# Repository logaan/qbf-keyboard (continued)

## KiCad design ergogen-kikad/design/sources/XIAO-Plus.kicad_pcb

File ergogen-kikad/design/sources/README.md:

# Controller source snapshot

`XIAO-Plus.kicad_pcb` and `XIAO-Plus.kicad_sch` are unmodified Seeed reference-project snapshots linked by the [official XIAO BLE documentation](https://wiki.seeedstudio.com/XIAO_BLE/). Their SHA-256 hashes are recorded in `../assembly.json`. The shared project contains optional Sense components; its footprint locations are dimensional references, not a guarantee of non-Sense population or exact supplied-module heights.

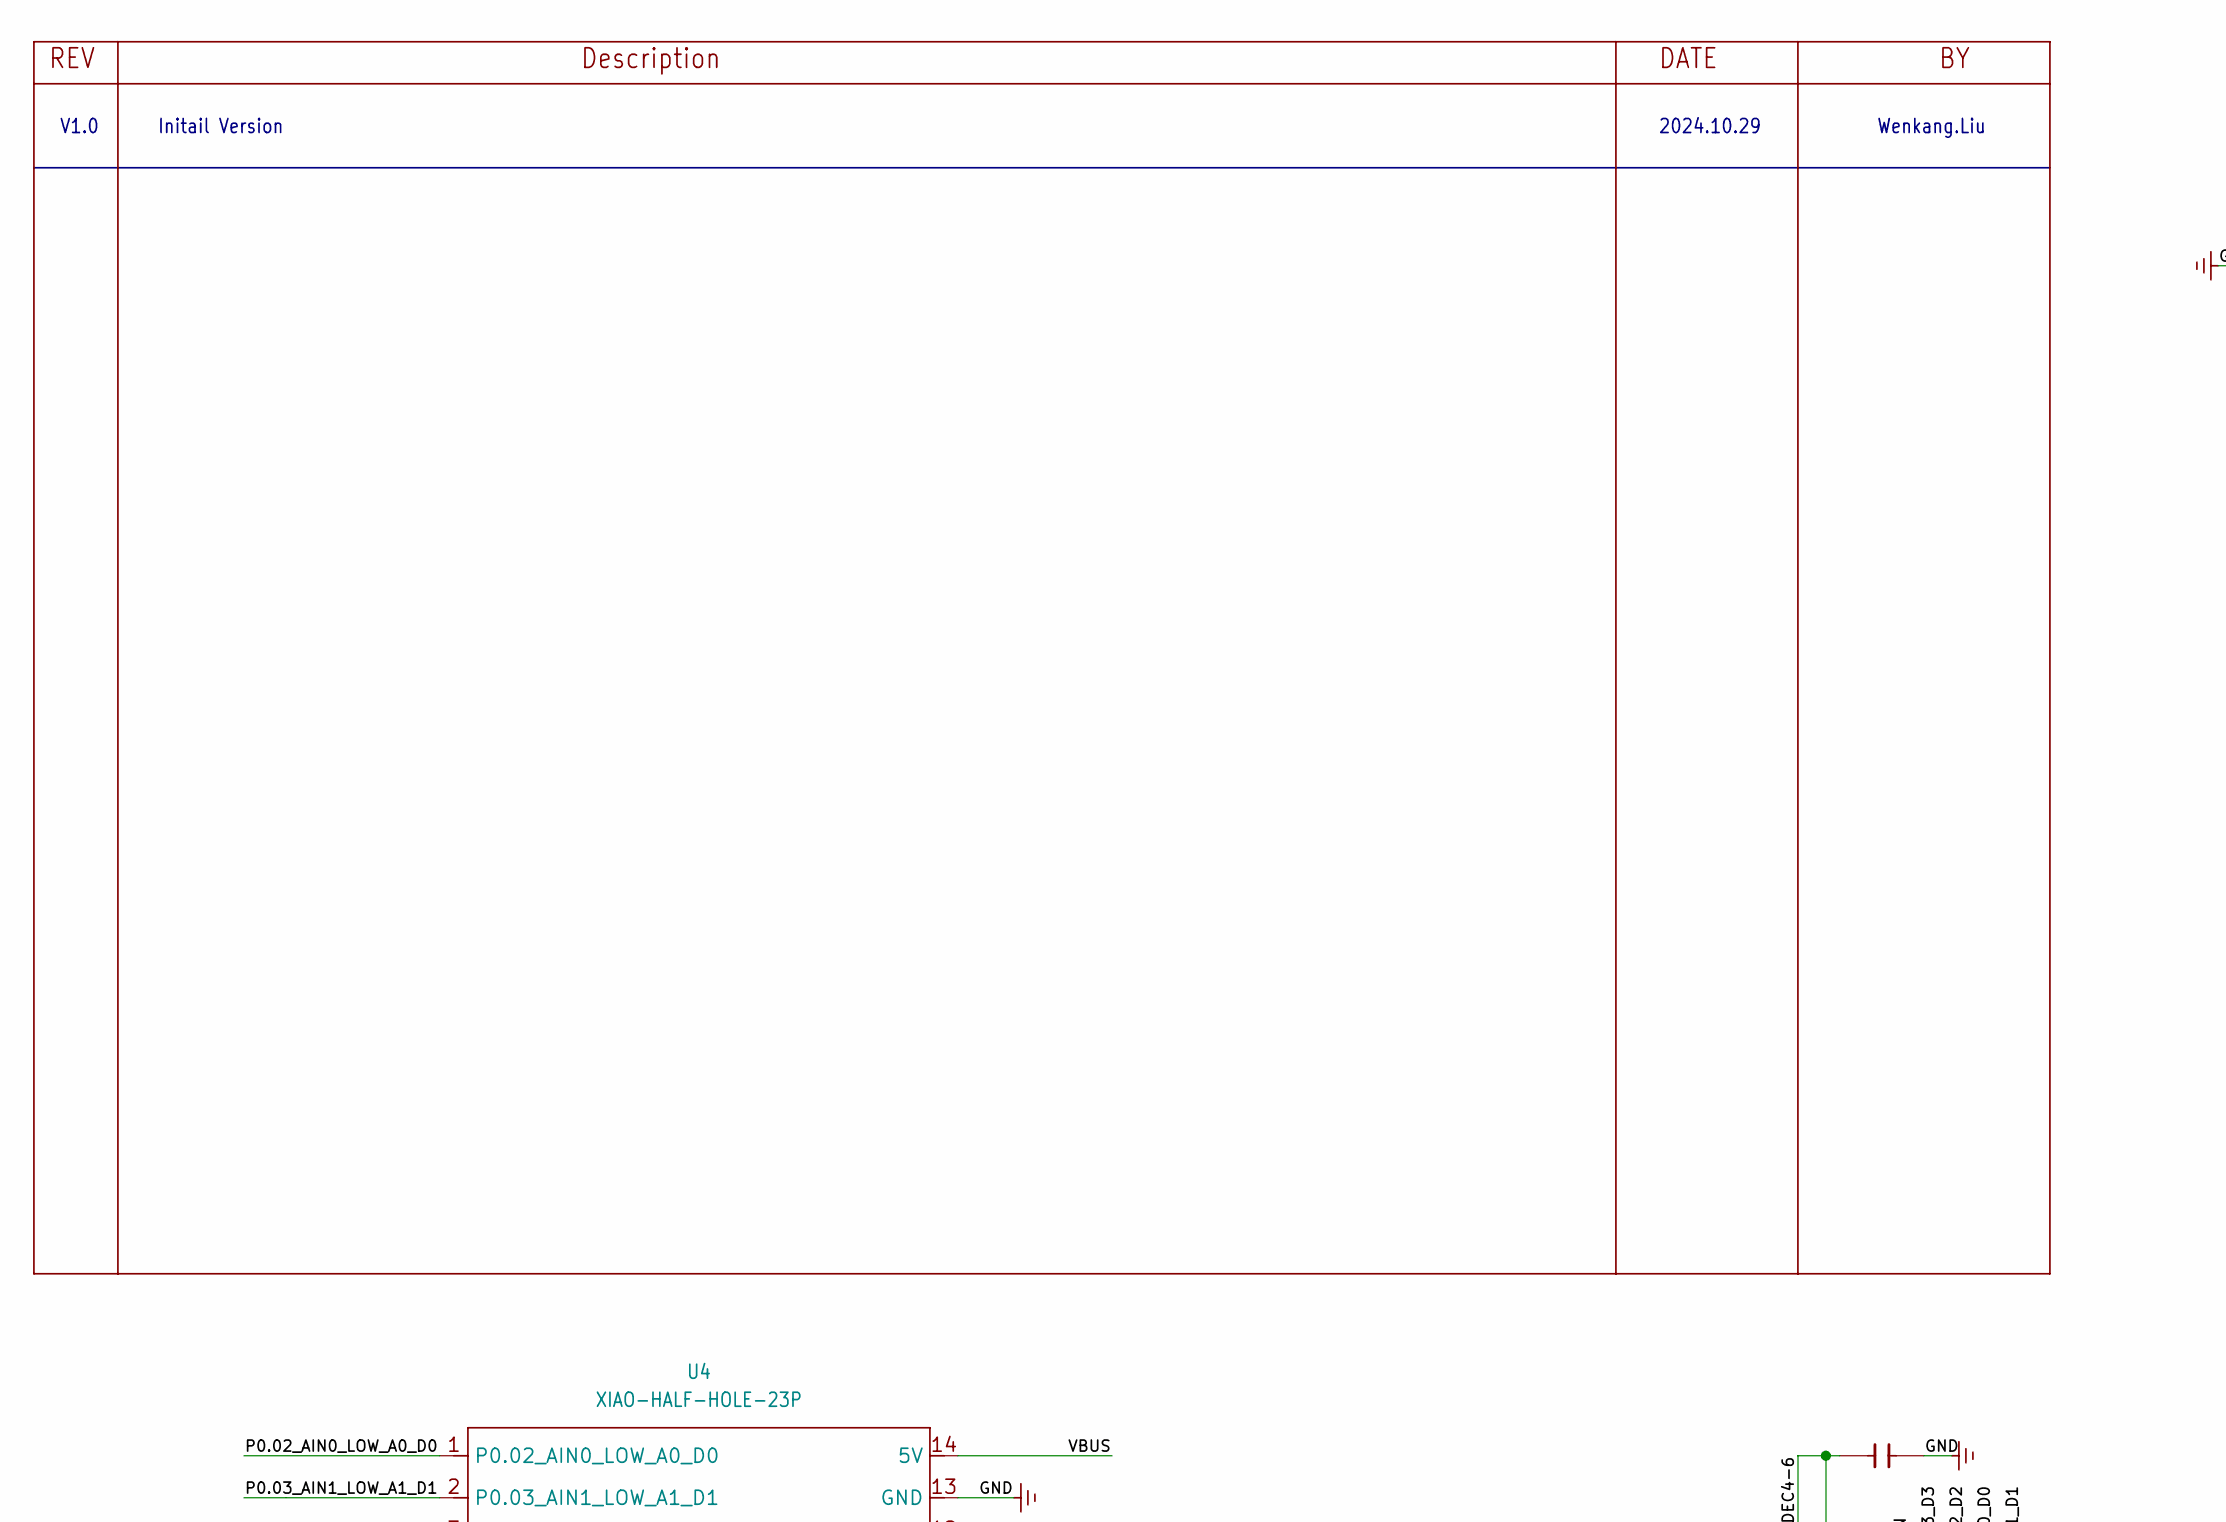
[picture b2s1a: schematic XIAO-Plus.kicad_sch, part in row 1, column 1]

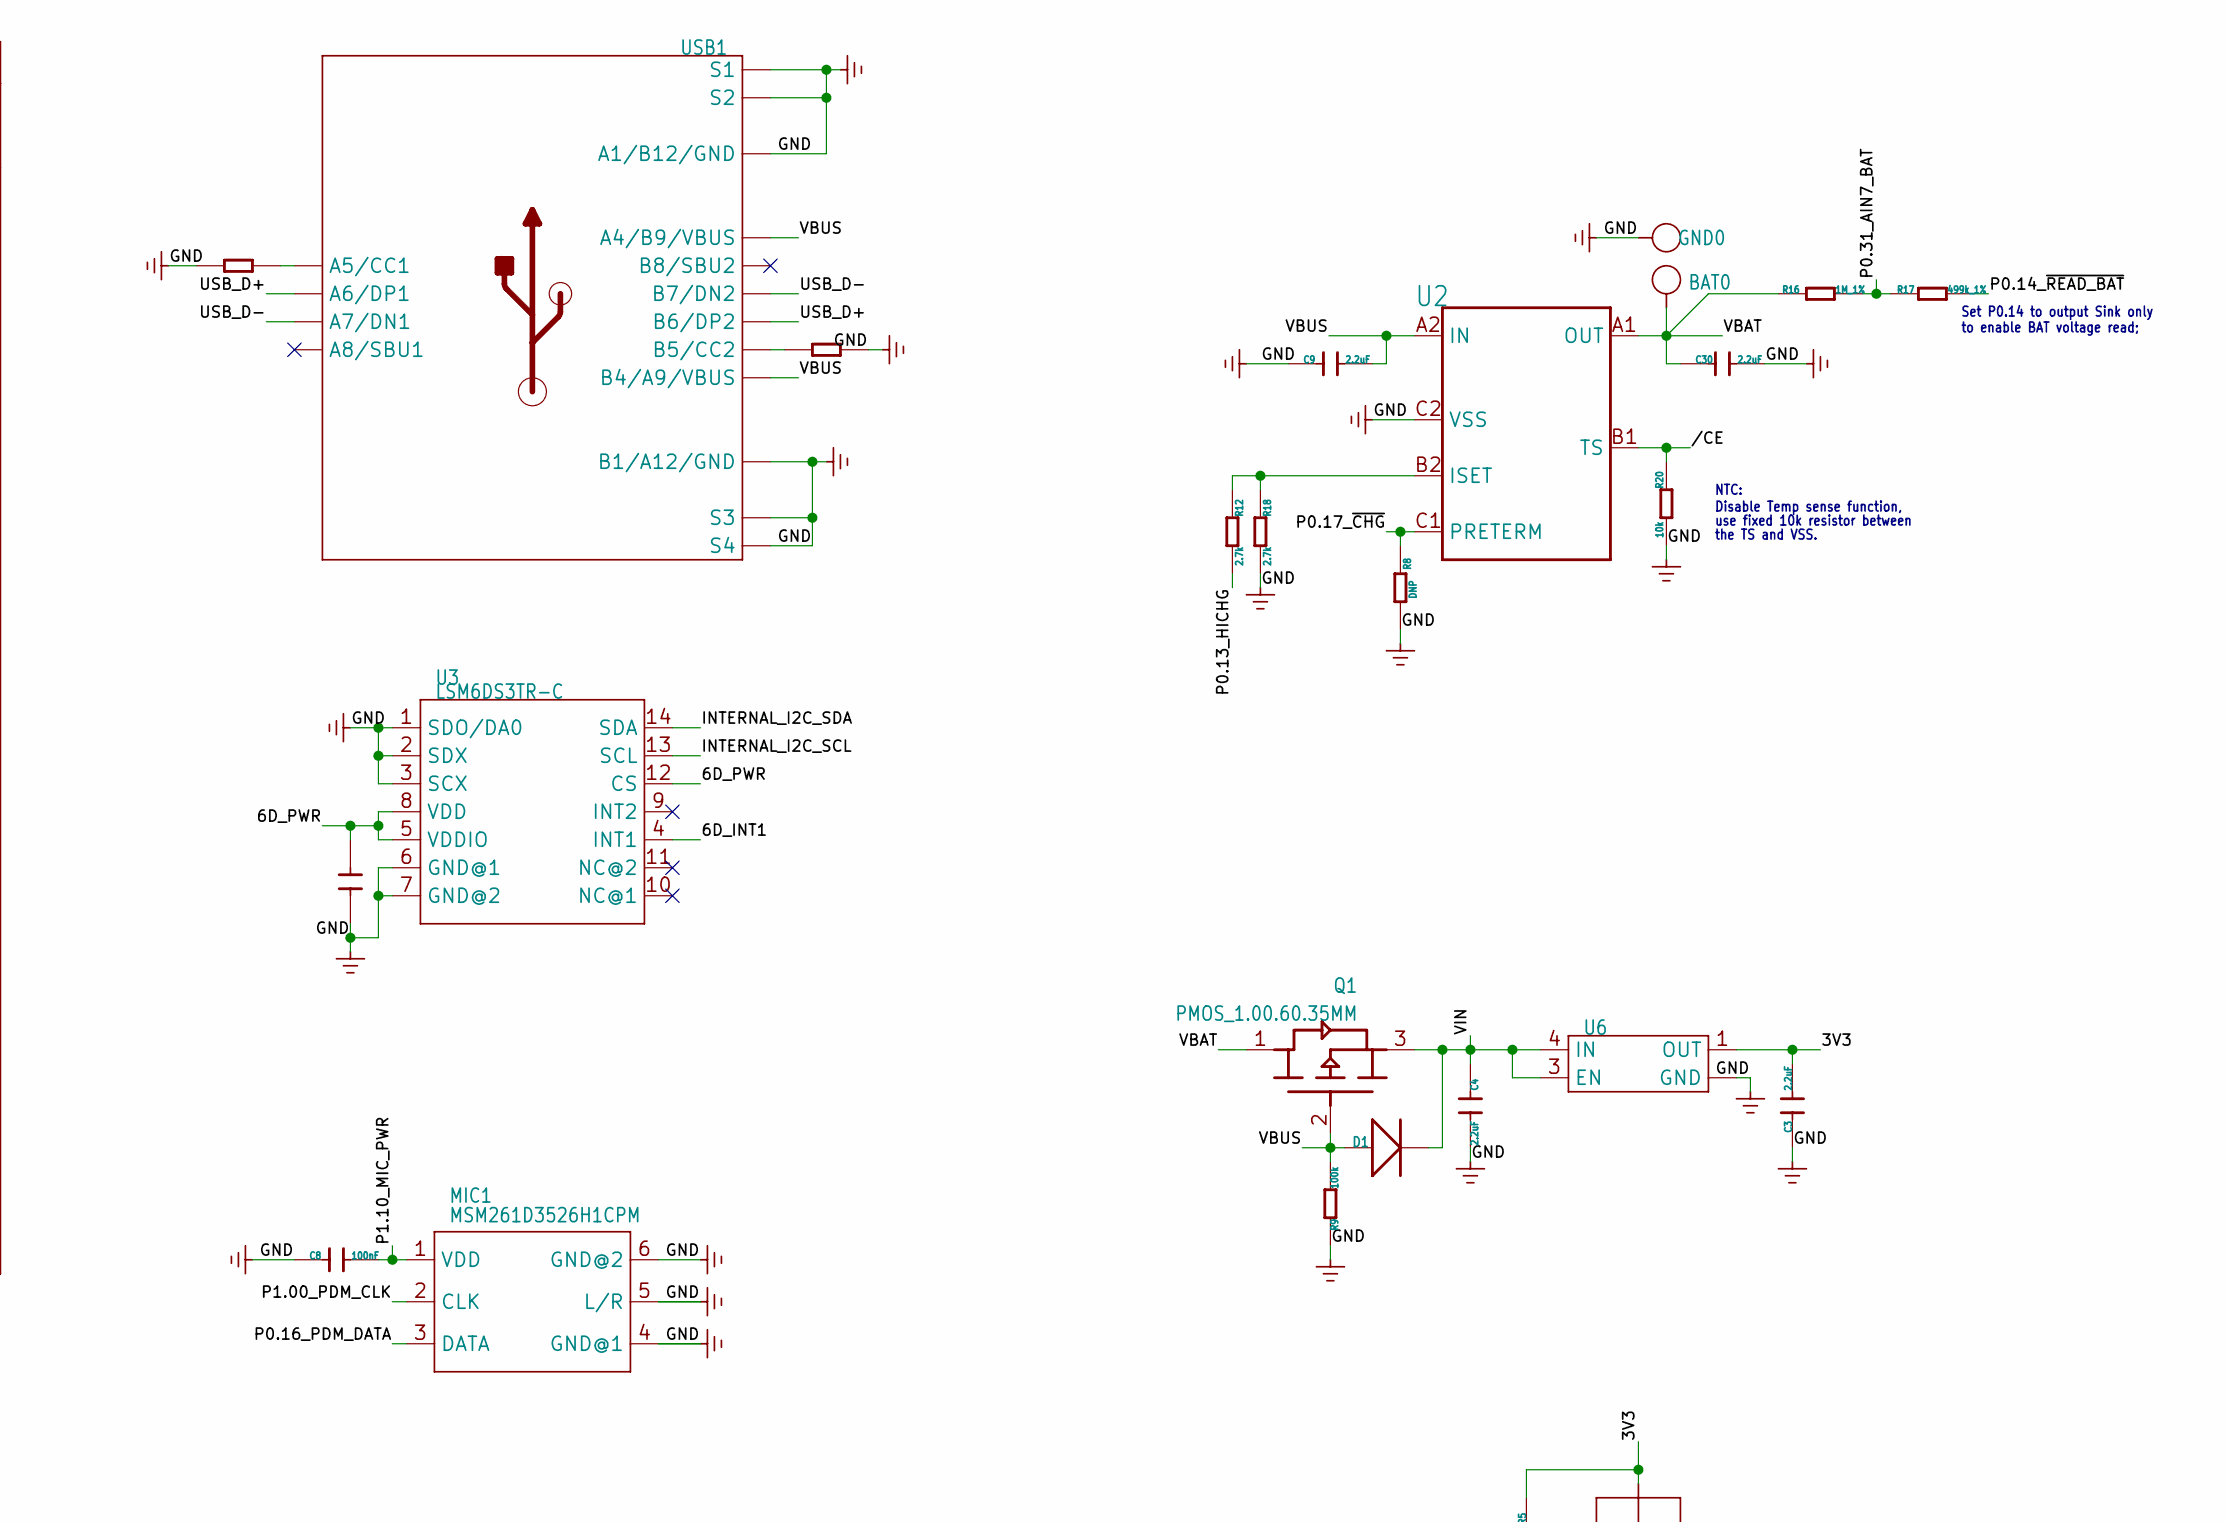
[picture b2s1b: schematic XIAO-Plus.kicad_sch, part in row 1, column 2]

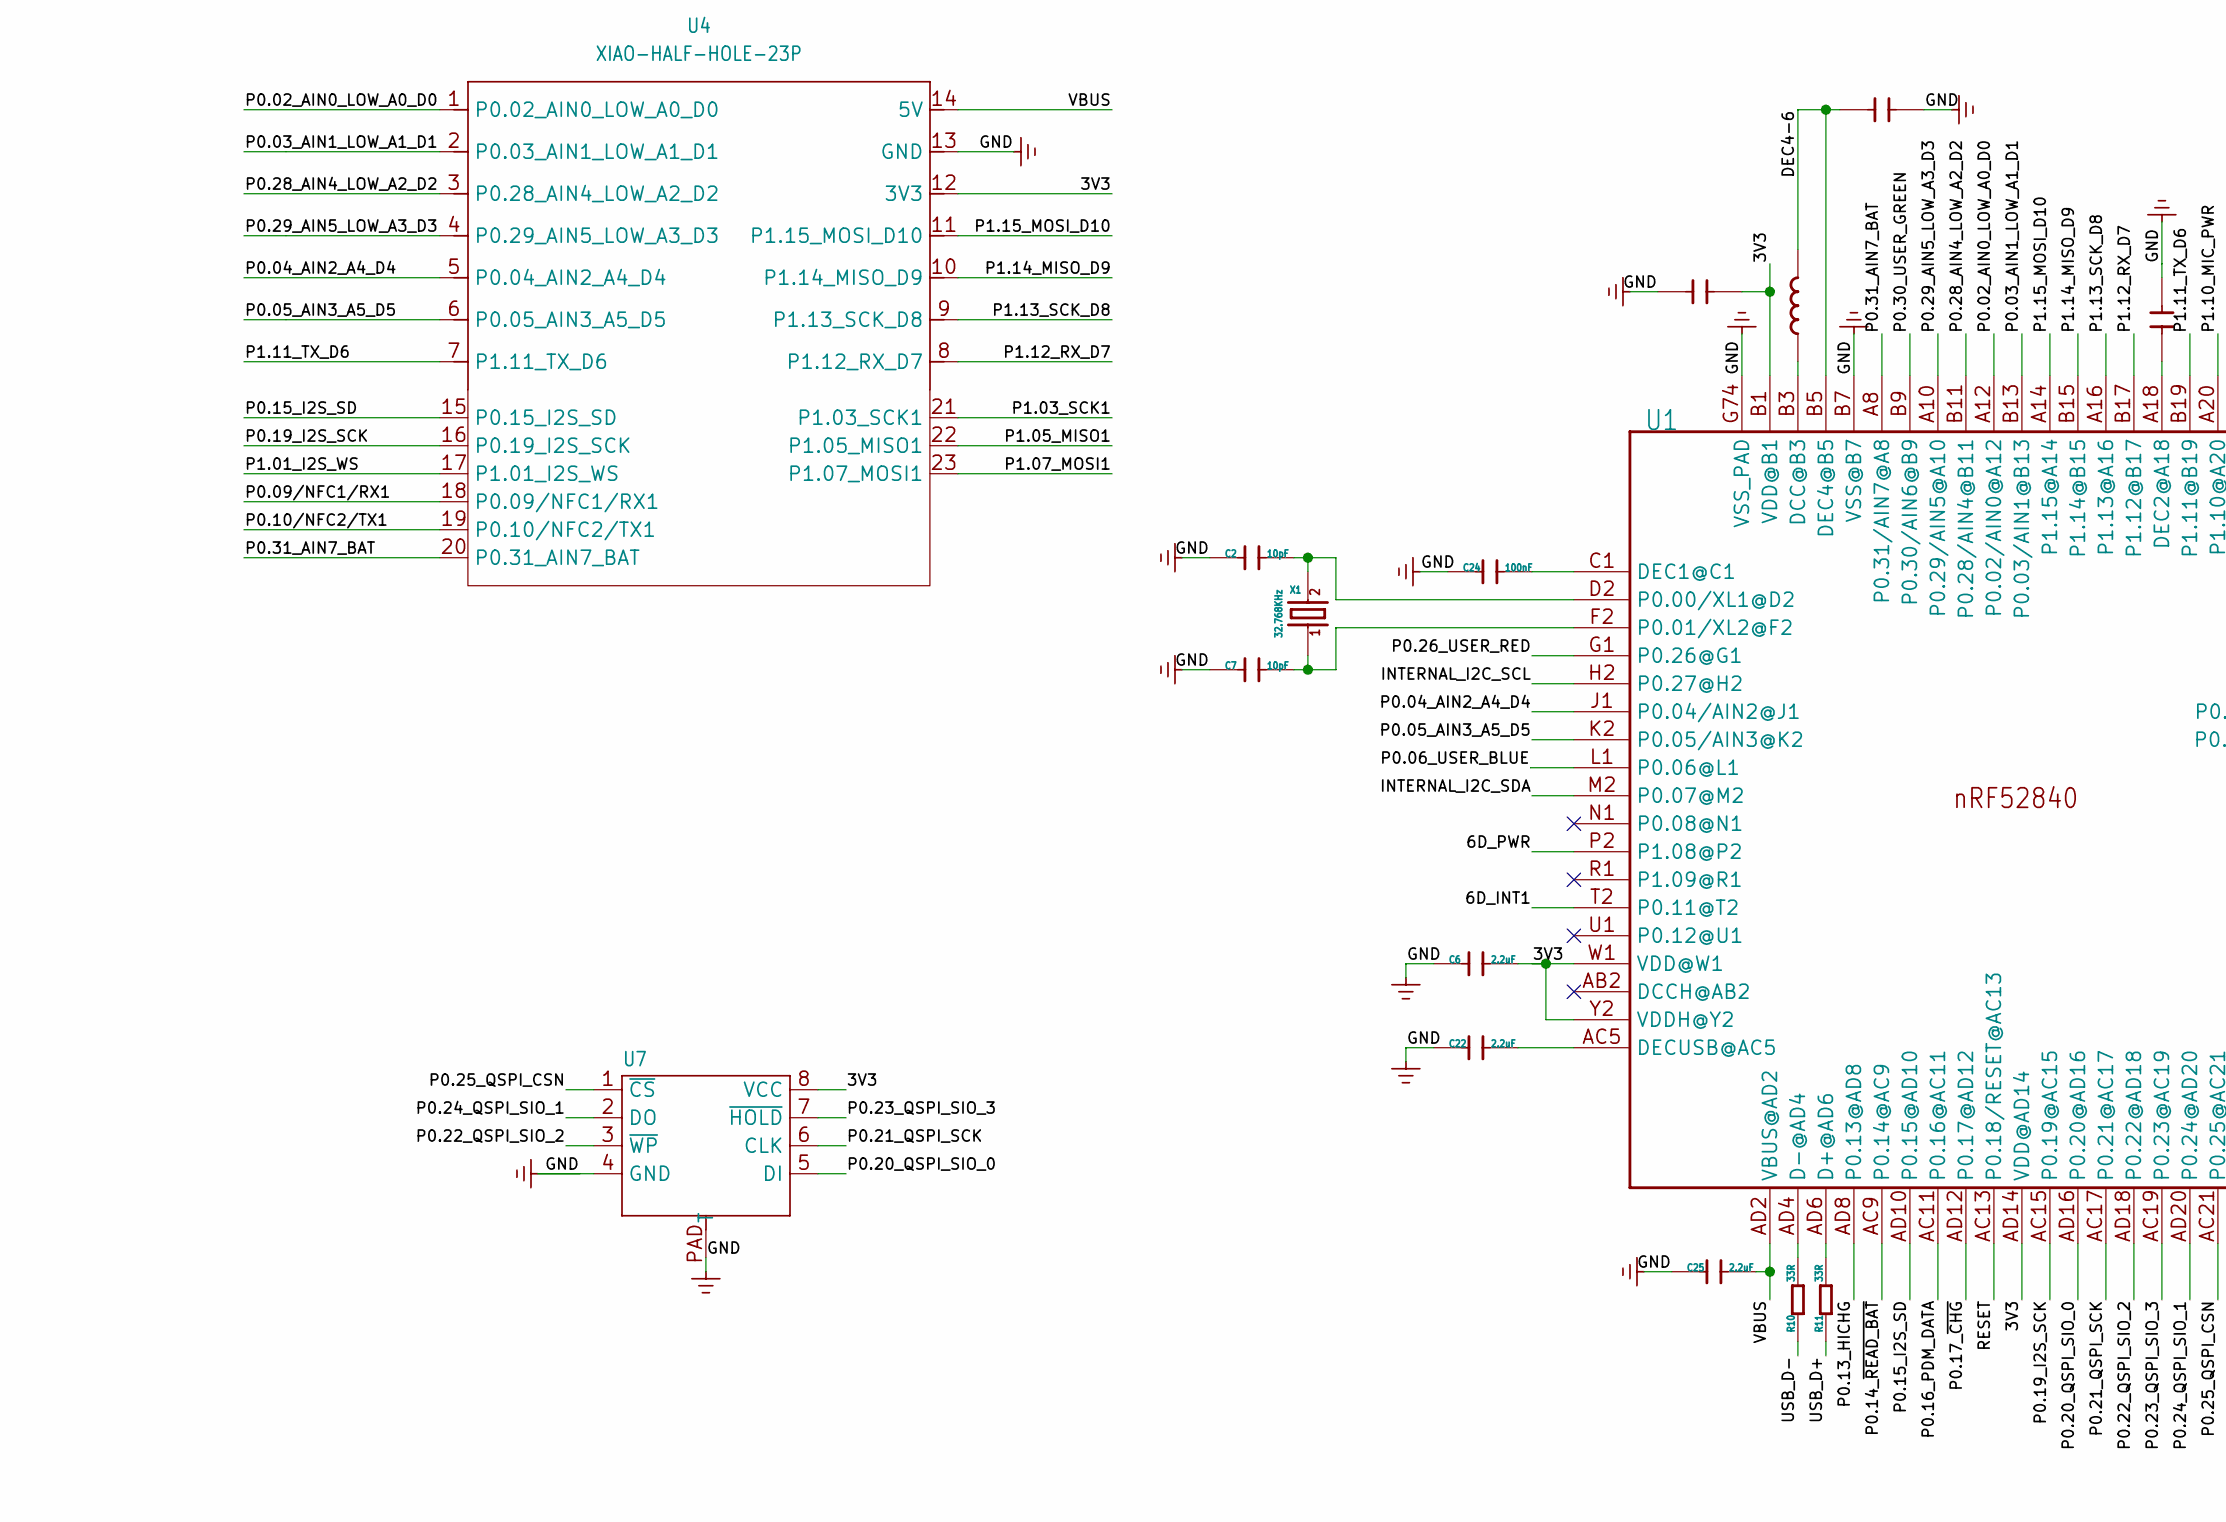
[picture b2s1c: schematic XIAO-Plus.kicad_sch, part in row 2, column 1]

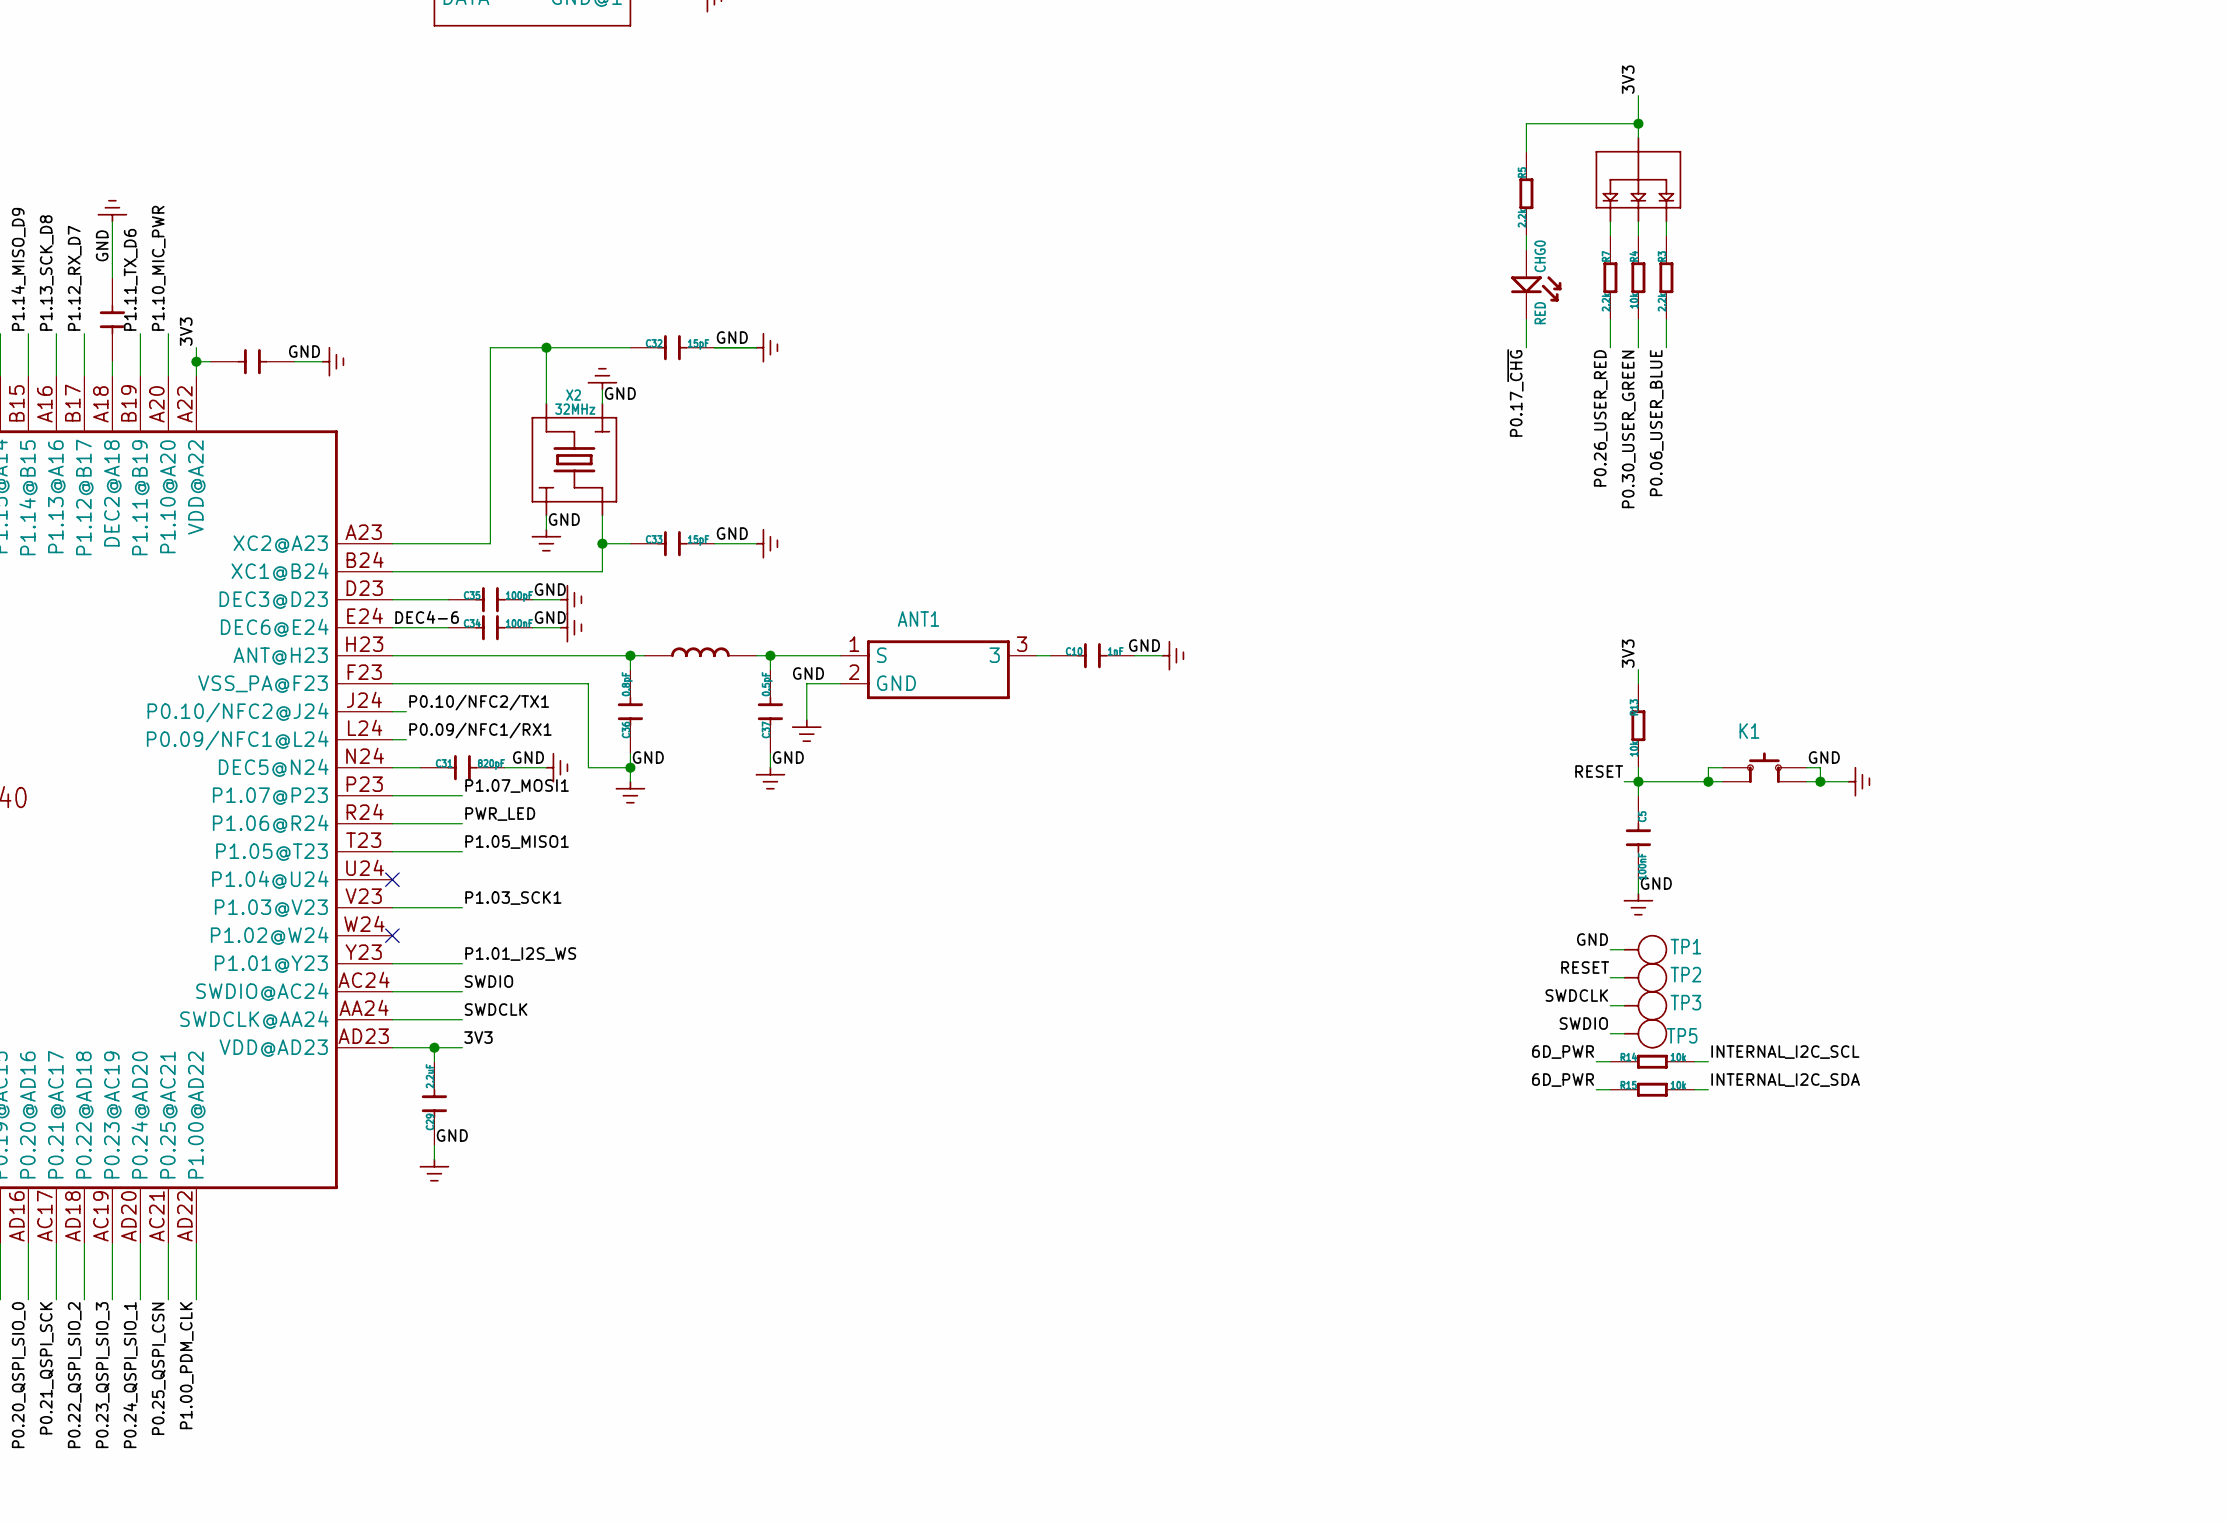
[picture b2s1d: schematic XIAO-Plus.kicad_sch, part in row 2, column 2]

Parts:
ANT1: ANTENNA-AN3216; ANT-SMD3P-3.2X1.6X1.04MM
BAT0: TEST-POINT'4080'; TP-80X40MIL
C1, C5, C8, C24, C34: 100nF; C0201
C2, C7: 10pF; C0201
C3, C4, C6, C9, C22, C25, C29, C30, C39, C41, C42: 2.2uF; C0201
C10: 1nF; C0402
C31: 820pF; C0201
C32, C33: 15pF; C0201
C35: 100pF; C0201
C36: 0.8pF; C0201
C37: 0.5pF; C0201
C38: 4.7nH; L0201
C40: DNP; C0201
CHG0: RED; LED-0402
D1: DIODE'0603'; SOD-523
GND0: GND; TP-80X40MIL
K1: BUTTON-4P; SW4-SMD-2.8-2.6X1.6X0.53MM
L3: 10uH; L0603
MIC1: MSM261D3526H1CPM; MIC6P-3.5X2.65X0.94MM
Q1: PMOS_1.00.60.35MM; PMOS_1.0*0.6*0.35MM
R1, R2: 5.1k; R0201
R3, R5, R7: 2.2k; R0201
R4, R13, R14, R15, R20: 10k; R0201
R8: DNP; R0201
R9: 100k; R0201
R10, R11: 33R; R0201
R12, R18: 2.7k; R0201
R16: 1M_1%; R0201
R17: 499k_1%; R0201
RGB6: RGB; 4P1010
TP1, TP2, TP3, TP5: TEST-POINT'4545'; TP-D45MIL
U1: NRF52840_QF; AQFN50P700X700X85_HS-74N
U2: BQ25100; BQ25101_DSBGA_6_BQ25101
U3: LSM6DS3TR-C; LGA14-0.5-2.5X3X0.86MM
U4: XIAO-HALF-HOLE-23P; MOUDLE23P-XIAO-HALF-HOLE
U6: 3.3V; X2SON-4
U7: DNP; USON2X3_8
USB1: USB2.0-TYPE-C
X1: 32.768KHz; X2-SMD-L1.6X1.0X0.5MM
X2: 32MHz; 4P1612

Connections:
/3V3: C3.2, C6.2, C29.2, C39.1, C41.2, R5.1, R13.1, RGB6.+, U1.A22 (VDD@A22), U1.AD14 (VDD@AD14), U1.AD23 (VDD@AD23), U1.B1 (VDD@B1), U1.W1 (VDD@W1), U1.Y2 (VDDH@Y2), U4.12 (3V3), U6.1 (OUT), U7.8 (VCC)
/6D_INT1: U1.T2 (P0.11@T2), U3.4 (INT1)
/6D_PWR: C1.2, R14.1, R15.1, U1.P2 (P1.08@P2), U3.5 (VDDIO), U3.8 (VDD), U3.12 (CS)
/DEC4-6: C34.1, C42.1, L3.2, U1.B5 (DEC4@B5), U1.E24 (DEC6@E24)
/INTERNAL_I2C_SCL: R14.2, U1.H2 (P0.27@H2), U3.13 (SCL)
/INTERNAL_I2C_SDA: R15.2, U1.M2 (P0.07@M2), U3.14 (SDA)
/P0.02_AIN0_LOW_A0_D0: U1.A12 (P0.02/AIN0@A12), U4.1 (PA02_A0_D0)
/P0.03_AIN1_LOW_A1_D1: U1.B13 (P0.03/AIN1@B13), U4.2 (PA4_A1_D1)
/P0.04_AIN2_A4_D4: U1.J1 (P0.04/AIN2@J1), U4.5 (PA8_A4_D4_SDA)
/P0.05_AIN3_A5_D5: U1.K2 (P0.05/AIN3@K2), U4.6 (PA9_A5_D5_SCL)
/P0.06_USER_BLUE: R3.2, U1.L1 (P0.06@L1)
/P0.09/NFC1/RX1: U1.L24 (P0.09/NFC1@L24), U4.18
/P0.10/NFC2/TX1: U1.J24 (P0.10/NFC2@J24), U4.19
/P0.13_HICHG: R12.2, U1.AD8 (P0.13@AD8)
/P0.14_~READ_BAT: R17.2, U1.AC9 (P0.14@AC9)
/P0.15_I2S_SD: U1.AD10 (P0.15@AD10), U4.15
/P0.16_PDM_DATA: MIC1.3 (DATA), U1.AC11 (P0.16@AC11)
/P0.17_~CHG: CHG0.-, R8.1, U1.AD12 (P0.17@AD12), U2.C1 (PRETERM)
/P0.19_I2S_SCK: U1.AC15 (P0.19@AC15), U4.16
/P0.20_QSPI_SIO_0: U1.AD16 (P0.20@AD16), U7.5 (DI)
/P0.21_QSPI_SCK: U1.AC17 (P0.21@AC17), U7.6 (CLK)
/P0.22_QSPI_SIO_2: U1.AD18 (P0.22@AD18), U7.3 (~WP)
/P0.23_QSPI_SIO_3: U1.AC19 (P0.23@AC19), U7.7 (~HOLD)
/P0.24_QSPI_SIO_1: U1.AD20 (P0.24@AD20), U7.2 (DO)
/P0.25_QSPI_CSN: U1.AC21 (P0.25@AC21), U7.1 (~CS)
/P0.26_USER_RED: R7.2, U1.G1 (P0.26@G1)
/P0.28_AIN4_LOW_A2_D2: U1.B11 (P0.28/AIN4@B11), U4.3 (PA10_A2_D2)
/P0.29_AIN5_LOW_A3_D3: U1.A10 (P0.29/AIN5@A10), U4.4 (PA11_A3_D3)
/P0.30_USER_GREEN: R4.2, U1.B9 (P0.30/AIN6@B9)
/P0.31_AIN7_BAT: R16.2, R17.1, U1.A8 (P0.31/AIN7@A8), U4.20
/P1.00_PDM_CLK: MIC1.2 (CLK), U1.AD22 (P1.00@AD22)
/P1.01_I2S_WS: U1.Y23 (P1.01@Y23), U4.17
/P1.03_SCK1: U1.V23 (P1.03@V23), U4.21
/P1.05_MISO1: U1.T23 (P1.05@T23), U4.22
/P1.07_MOSI1: U1.P23 (P1.07@P23), U4.23
/P1.10_MIC_PWR: C8.2, MIC1.1 (VDD), U1.A20 (P1.10@A20)
/P1.11_TX_D6: U1.B19 (P1.11@B19), U4.7 (PB08_A6_D6_TX)
/P1.12_RX_D7: U1.B17 (P1.12@B17), U4.8 (PB09_A7_D7_RX)
/P1.13_SCK_D8: U1.A16 (P1.13@A16), U4.9 (PA7_A8_D8_SCK)
/P1.14_MISO_D9: U1.B15 (P1.14@B15), U4.10 (PA5_A9_D9_MISO)
/P1.15_MOSI_D10: U1.A14 (P1.15@A14), U4.11 (PA6_A10_D10_MOSI)
/PWR_LED: U1.R24 (P1.06@R24)
/RESET: C5.1, K1.1 (A0), K1.3 (A1), R13.2, TP2.T, U1.AC13 (P0.18/RESET@AC13)
/SWDCLK: TP3.T, U1.AA24 (SWDCLK@AA24)
/SWDIO: TP5.T, U1.AC24 (SWDIO@AC24)
/USB_D+: R11.1, USB1.A6 (A6/DP1), USB1.B6 (B6/DP2)
/USB_D-: R10.1, USB1.A7 (A7/DN1), USB1.B7 (B7/DN2)
/VBAT: BAT0.1 (T), C30.1, Q1.1 (D), R16.1, U2.A1 (OUT)
/VBUS: C9.2, C25.2, D1.+, Q1.2 (G), R9.2, U1.AD2 (VBUS@AD2), U2.A2 (IN), U4.14 (5V), USB1.A4_B9 (A4/B9/VBUS), USB1.B4_A9 (B4/A9/VBUS)
/VIN: C4.1, D1.-, Q1.3 (S), U6.3 (EN), U6.4 (IN)
//CE: R20.1, U2.B1 (TS)
GND_POWER: ANT1.2 (GND), C1.1, C2.1, C3.1, C4.2, C5.2, C6.1, C7.1, C8.1, C9.1, C10.2, C22.1, C24.1, C25.1, C29.1, C30.2, C31.2, C32.2, C33.2, C34.2, C35.2, C36.1, C37.1, C39.2, C40.2, C41.1, C42.2, GND0.1 (T), K1.2 (B0), K1.4 (B1), MIC1.4 (GND@1), MIC1.5 (L/R), MIC1.6 (GND@2), R1.2, R2.1, R8.2, R9.1, R18.2, R20.2, TP1.T, U1.B7 (VSS@B7), U1.F23 (VSS_PA@F23), U1.G74 (VSS_PAD), U2.C2 (VSS), U3.1 (SDO/DA0), U3.2 (SDX), U3.3 (SCX), U3.6 (GND@1), U3.7 (GND@2), U4.13 (GND), U6.2 (GND), U6.T (GND), U7.4 (GND), U7.PAD (T), USB1.A1_B12 (A1/B12/GND), USB1.B1_A12 (B1/A12/GND), USB1.S1, USB1.S2, USB1.S3, USB1.S4, USB1.S5 (S1), USB1.S6 (S2), X2.2 (1), X2.4 (3)
unnamed: ANT1.3, C10.1
unnamed: ANT1.1 (S), C37.2, C38.2
unnamed: CHG0.+, R5.2
unnamed: R3.1, RGB6.B-
unnamed: R4.1, RGB6.G-
unnamed: R7.1, RGB6.R-
unnamed: C36.2, C38.1, U1.H23 (ANT@H23)
unnamed: R11.2, U1.AD6 (D+@AD6)
unnamed: R10.2, U1.AD4 (D-@AD4)
unnamed: L3.1, U1.B3 (DCC@B3)
unnamed: C24.2, U1.C1 (DEC1@C1)
unnamed: C40.1, U1.A18 (DEC2@A18)
unnamed: C35.1, U1.D23 (DEC3@D23)
unnamed: C31.1, U1.N24 (DEC5@N24)
unnamed: C22.2, U1.AC5 (DECUSB@AC5)
unnamed: C2.2, U1.D2 (P0.00/XL1@D2), X1.2
unnamed: C7.2, U1.F2 (P0.01/XL2@F2), X1.1
unnamed: C33.1, U1.B24 (XC1@B24), X2.1 (2)
unnamed: C32.1, U1.A23 (XC2@A23), X2.3 (4)
unnamed: R12.1, R18.1, U2.B2 (ISET)
unnamed: R1.1, USB1.A5 (A5/CC1)
unnamed: R2.2, USB1.B5 (B5/CC2)

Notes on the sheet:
the TS and VSS.
Disable Temp sense function,
NTC:
use fixed 10k resistor between
Initail Version
Wenkang.Liu
V1.0
2024.10.29
Set P0.14 to output Sink only to enable BAT voltage read;

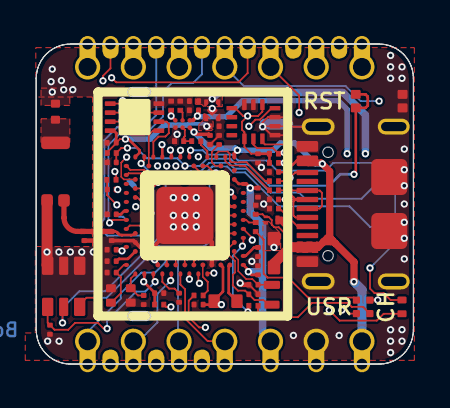
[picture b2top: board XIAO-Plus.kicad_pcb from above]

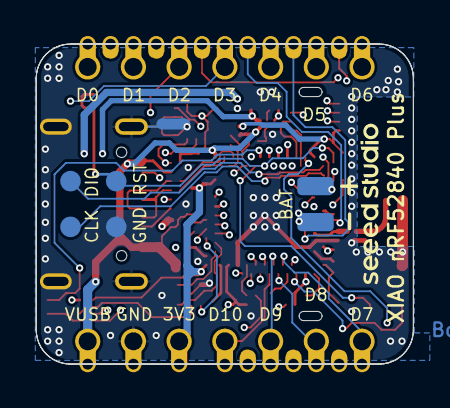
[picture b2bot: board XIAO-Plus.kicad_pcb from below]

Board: 4 copper layers, 21.0 x 17.8 mm, 68 parts (6 on the bottom side), 73 nets.

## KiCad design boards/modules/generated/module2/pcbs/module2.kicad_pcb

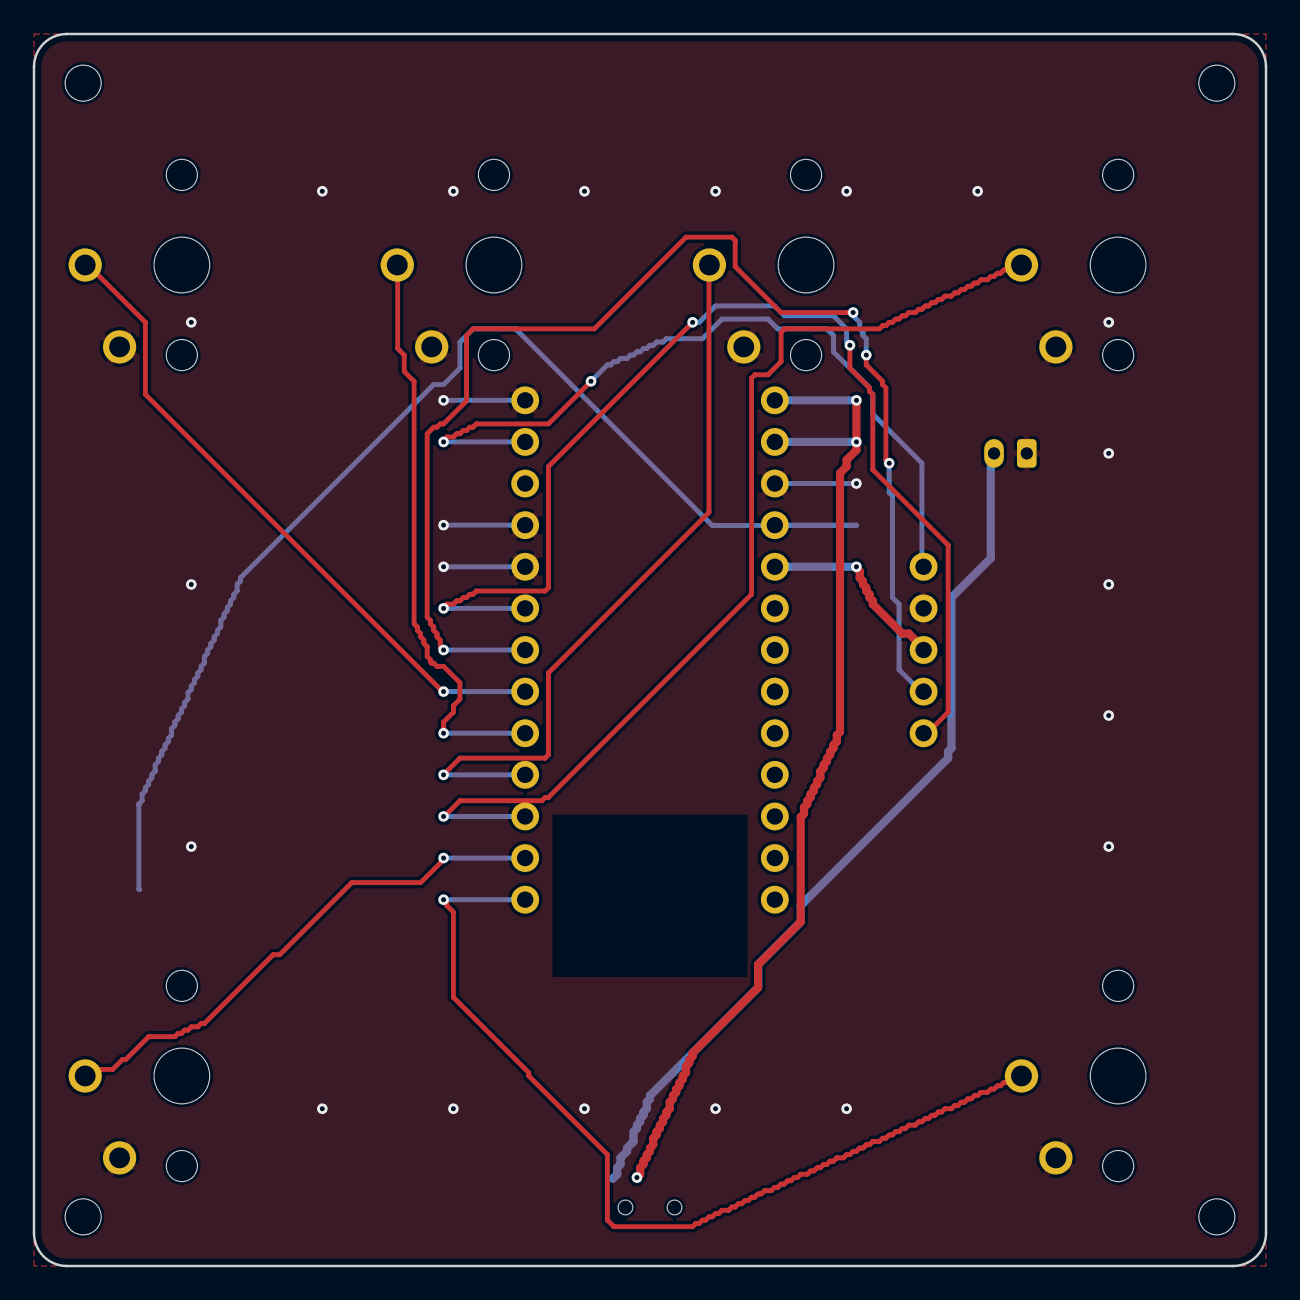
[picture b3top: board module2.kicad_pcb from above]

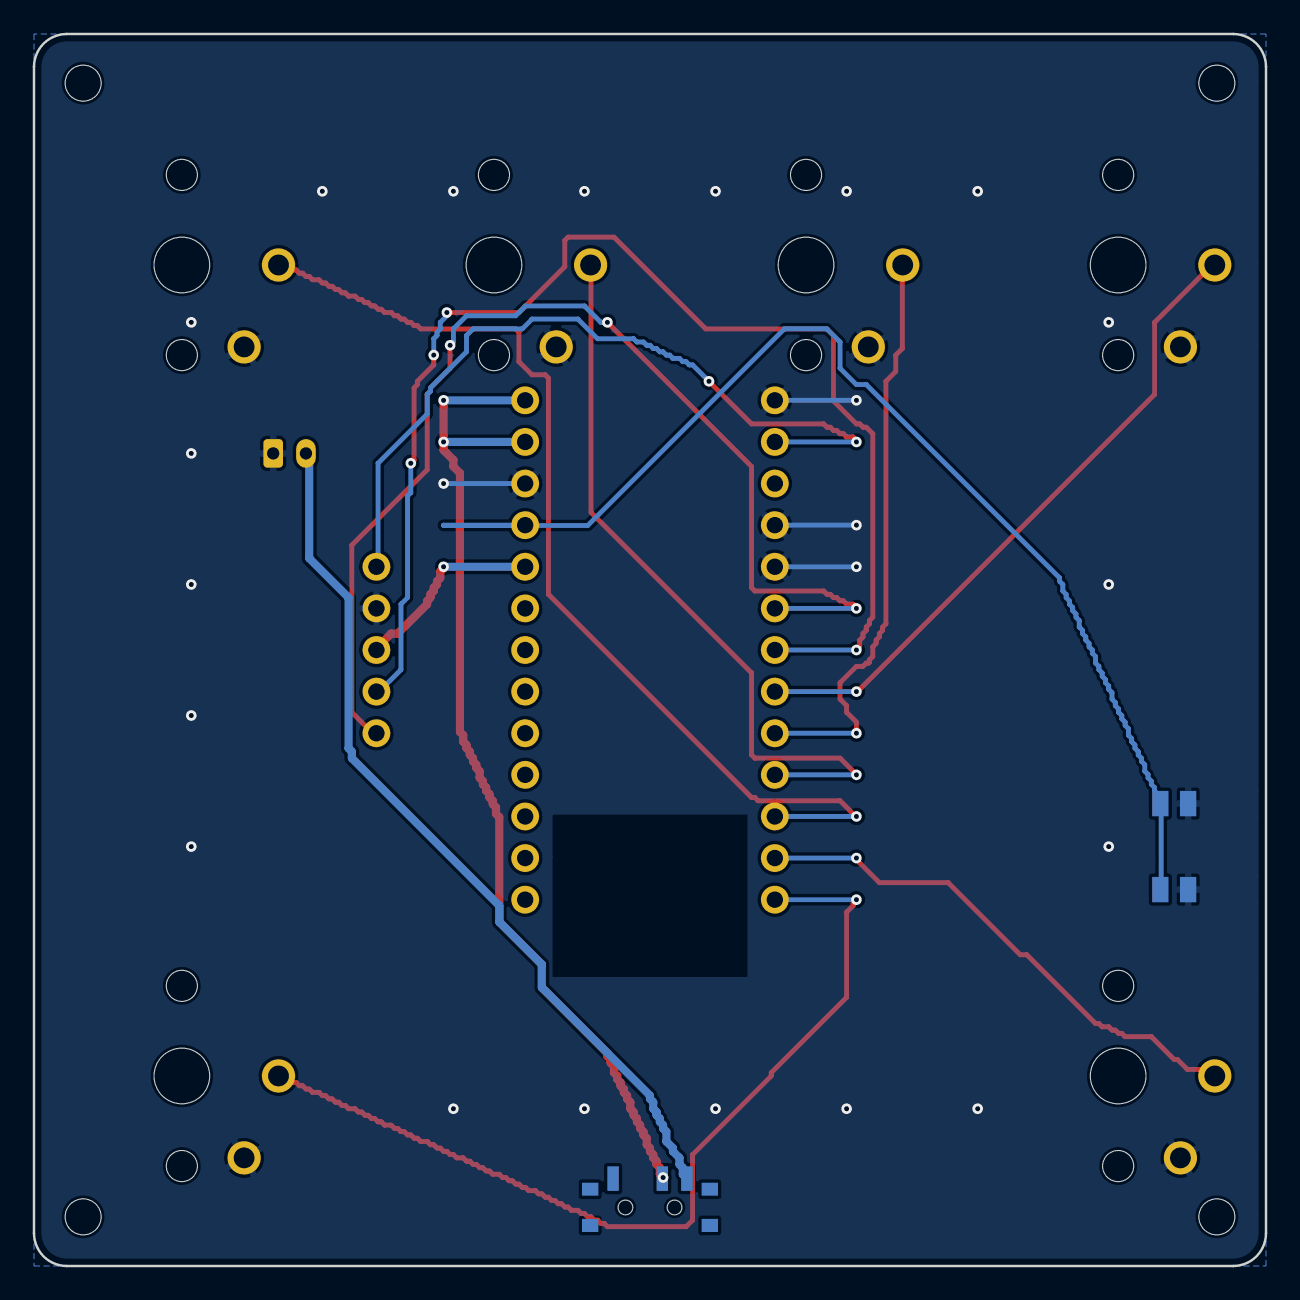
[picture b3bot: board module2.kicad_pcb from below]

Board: 2 copper layers, 75.2 x 75.2 mm, 15 parts (8 on the bottom side), 14 nets.

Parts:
DISP1: display_nice_view
JST1: battery_connector_jst_ph_2
MCU1: mcu_nice_nano
MH1, MH2, MH3, MH4: mounting_hole_npth
PWR1: power_switch_smd_side
RST1: reset_switch_smd_side
S1, S2, S3, S4, S5, S6: switch_choc_v1_v2

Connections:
3V3: DISP1.3, MCU1.4
BAT_P: JST1.2, PWR1.3
DISPLAY_CS: DISP1.5, MCU1.24
DISPLAY_MOSI: DISP1.1, MCU1.20
DISPLAY_SCK: DISP1.2, MCU1.19
GND: DISP1.4, JST1.1, MCU1.2, MCU1.21, MCU1.22, MCU1.25, RST1.1, RST1.3, S1.1, S2.1, S3.1, S4.1, S5.1, S6.1
RST: MCU1.3, RST1.2, RST1.4
VBAT: MCU1.1, MCU1.26, PWR1.2
key_r1_c1: MCU1.18, S1.2
key_r1_c2: MCU1.17, S2.2
key_r1_c3: MCU1.16, S3.2
key_r1_c4: MCU1.15, S4.2
key_r2_c1: MCU1.14, S5.2
key_r2_c4: MCU1.13, S6.2
